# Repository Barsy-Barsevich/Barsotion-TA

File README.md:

# Barsotion-TA
Board computer for model rockets, the 11th board after Berkut

## ⚡️Features
- Dual-core 240MHz Xtensa processor (in ESP32-S3)
- 512 MB log flash
- Up to 8kHz IMU cycle frequency
- Barometer, thermometer, hygrometer
- Onboard DC-DC pull-up converter for servos
- 2.4GHz Wi-Fi / Bluetooth / BLE antenna

## ⚡️Manual
- [EA&TA_user_manual_revD.pdf (newest revision)](./Manual/EA&TA_user_manual_revD.pdf)
- [EA&TA_user_manual_revC.pdf](./Manual/EA&TA_user_manual_revC.pdf)
- [EA&TA_user_manual_preliminary_edition_revB.pdf](./Manual/EA&TA_user_manual_preliminary_edition_revB.pdf)
- [EA&TA_user_manual_preliminary_edition_revA.pdf](./Manual/EA&TA_user_manual_preliminary_edition_revA.pdf)

## ⚡️Software
- [EA & TA software packet](https://github.com/Barsy-Barsevich/Barsotion-xA-software)

## ⚡️Continious progress
- [Previous board: Barsotion-EA](https://github.com/Barsy-Barsevich/Barsotion-EA)
- [Previous board: Barsotion-AH4](https://github.com/Barsy-Barsevich/Barsotion-AH4)

## ⚡️Schematic
[Full electrical schematic in .pdf](./Schematic/Barsotion-TA_Schematic_v1.6.pdf)

## ⚡️Parameters
- Microcontroller: ESP32-S3FN8 (2x Xtensa LX7 core)
- Clock frequency: 240MHz
- Gyroscope: on-board ICM-42688-P (SPI, interrupt channel)
- Barometer: on-board, BMP388 (I2C)
- Hygrometer: on-board, AHT20 (I2C)
- Memory: 4Gbit SPI NAND Flash W25N04KVZEIG (Quad SPI)
- Quartz Gyroscope's ODR frequency stabilization
- 2.4GHz Wi-Fi / Bluetooth / BLE antenna

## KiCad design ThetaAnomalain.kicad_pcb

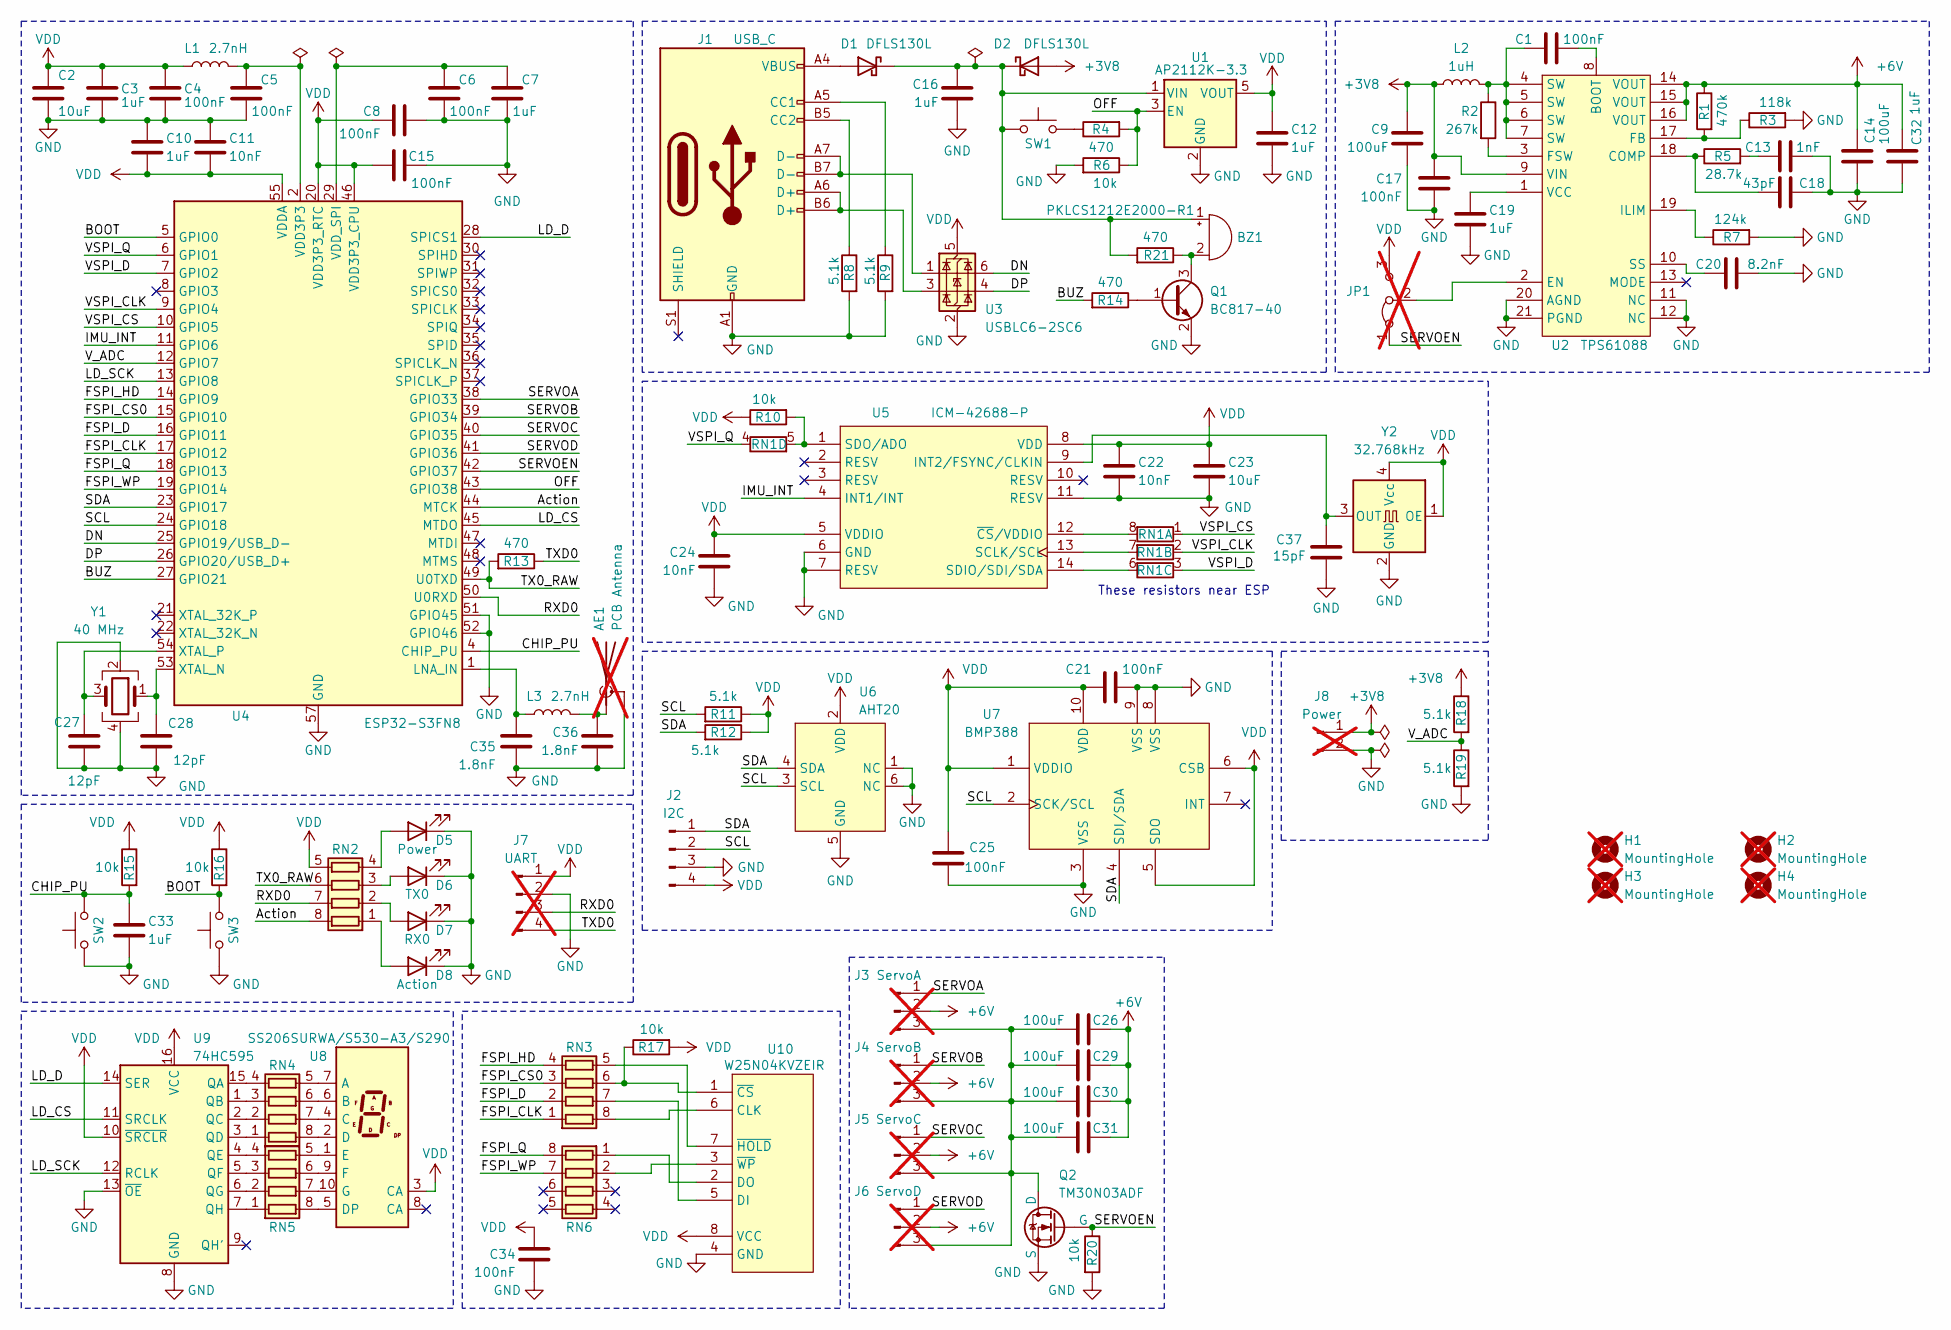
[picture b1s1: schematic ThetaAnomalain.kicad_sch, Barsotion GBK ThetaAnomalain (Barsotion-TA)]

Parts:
AE1: PCB Antenna; Texas_SWRA117D_2.4GHz_Right; not fitted
BZ1: PKLCS1212E2000-R1; Buzzer_Murata_PKLCS1212E; Mfr.Part PKLCS1212E2000-R1
C1, C4, C5, C6, C8, C15, C17, C21, C25, C34: 100nF; C_0402_1005Metric
C2, C23: 10uF; C_0402_1005Metric
C3, C7, C10, C12, C16, C19, C32, C33: 1uF; C_0402_1005Metric
C9, C14, C26, C29, C30, C31: 100uF; C_1206_3216Metric
C11, C22, C24: 10nF; C_0402_1005Metric
C13: 1nF; C_0402_1005Metric
C18: 43pF; C_0402_1005Metric
C20: 8.2nF; C_0402_1005Metric
C27, C28: 12pF; C_0402_1005Metric
C35, C36: 1.8nF; C_0402_1005Metric
C37: 15pF; C_0402_1005Metric
D1, D2: DFLS130L; D_PowerDI-123
D5: Power; LED_0603_1608Metric; Mfr.Part TJ-S1608CY6T5ALC9Y-A5
D6: TX0; LED_0603_1608Metric; Mfr.Part TJ-S1608CY6T5ALC9Y-A5
D7: RX0; LED_0603_1608Metric; Mfr.Part TJ-S1608CY6T5ALC9Y-A5
D8: Action; LED_0603_1608Metric; Mfr.Part TJ-S1608CY6T5ALC9Y-A5
H1, H2, H3, H4: MountingHole; MountingHole_3.2mm_M3_Pad_Via; not fitted
J1: USB_C; USB_C_Receptacle_GCT_USB4105-xx-A_16P_TopMnt_Horizontal; Mfr.Part TYPE C-DB-116PWB
J2: I2C; JST_GH_SM04B-GHS-TB_1x04-1MP_P1.25mm_Horizontal; Mfr.Part A1257WR-S-4P
J3: ServoA; JST_XH_B3B-XH-A_1x03_P2.50mm_Vertical; not fitted
J4: ServoB; JST_XH_B3B-XH-A_1x03_P2.50mm_Vertical; not fitted
J5: ServoC; JST_XH_B3B-XH-A_1x03_P2.50mm_Vertical; not fitted
J6: ServoD; JST_XH_B3B-XH-A_1x03_P2.50mm_Vertical; not fitted
J7: UART; JST_XH_B4B-XH-A_1x04_P2.50mm_Vertical; not fitted
J8: Power; Battery_3V7_Cable_connector_v2; not fitted
JP1: Jumper_3_Bridged12; SolderJumper-3_P1.3mm_Bridged12_Pad1.0x1.5mm_NumberLabels; not fitted
L1, L3: 2.7nH; L_0402_1005Metric
L2: 1uH; L_APV_APH0630; Mfr.Part APH0630T1R0M
Q1: BC817-40; SOT-23
Q2: TM30N03ADF; PDFN3x3-8L; Mfr.Part TM30N03ADF
R1: 470k; R_0402_1005Metric
R2: 267k; R_0402_1005Metric
R3: 118k; R_0402_1005Metric
R4, R13, R14, R21: 470; R_0402_1005Metric
R5: 28.7k; R_0402_1005Metric
R6, R10, R15, R16, R17, R20: 10k; R_0402_1005Metric
R7: 124k; R_0402_1005Metric
R8, R9, R11, R12, R18, R19: 5.1k; R_0402_1005Metric
RN1: 47; R_Array_Convex_4x0402
RN2, RN4, RN5: 1k; R_Array_Convex_4x0402
RN3, RN6: 0; R_Array_Convex_4x0402
SW1, SW2, SW3: TS-1187A-B-A-B; SW_Push_1P1T_XKB_TS-1187A; Mfr.Part TS-1187A-B-A-B
U1: AP2112K-3.3; SOT-23-5; Mfr.Part AP2112K-3.3TRG1
U2: TPS61088; RHL0020A; Mfr.Part TPS61088RHLR
U3: USBLC6-2SC6; SOT-23-6; Mfr.Part USBLC6-2SC6
U4: ESP32-S3FN8; QFN-56-1EP_7x7mm_P0.4mm_EP4x4mm; Mfr.Part ESP32-S3FN8
U5: ICM-42688-P; LGA-14_3x2.5mm_P0.5mm_LayoutBorder3x4y; Mfr.Part ICM-42688-P
U6: AHT20; Mfr.Part AHT20
U7: BMP388; BMP388_v2; Mfr.Part BMP388
U8: SS206SURWA/S530-A3/S290; SS206SURWA; Mfr.Part SS206SURWA/S530-A3/S290
U9: 74HC595; TSSOP-16_4.4x5mm_P0.65mm; Mfr.Part SN74HC595PWR
U10: W25N04KVZEIR; WSON-8-1EP_8x6mm_P1.27mm_EP3.4x4.3mm; Mfr.Part W25N04KVZEIR
Y1: 40 MHz; Crystal_SMD_3225-4Pin_3.2x2.5mm; Mfr.Part X322540MPB4SI
Y2: 32.768kHz; Oscillator_SMD_SeikoEpson_SG8002CE-4Pin_3.2x2.5mm; Mfr.Part OK2EL89CJI-111YLC-32.768K

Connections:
+3V8: C9.1, C17.1, D2.2 (A), J8.1, L2.1, R18.1, U2.9 (VIN)
+6V: C14.1, C26.1, C29.1, C30.1, C31.1, C32.1, J3.2, J4.2, J5.2, J6.2, R1.1, U2.14 (VOUT), U2.15 (VOUT), U2.16 (VOUT)
/Action: RN2.8 (R1.2), U4.44 (MTCK)
/BOOT: R16.2, SW3.2, U4.5 (GPIO0)
/BUZ: R14.2, U4.27 (GPIO21)
/CHIP_PU: C33.1, R15.2, SW2.2, U4.4 (CHIP_PU)
/DN: U3.6 (I/O1), U4.25 (GPIO19/USB_D-)
/DP: U3.4 (I/O2), U4.26 (GPIO20/USB_D+)
/FSPI_CLK: RN3.1 (R1.1), U4.17 (GPIO12)
/FSPI_CS0: RN3.3 (R3.1), U4.15 (GPIO10)
/FSPI_D: RN3.2 (R2.1), U4.16 (GPIO11)
/FSPI_HD: RN3.4 (R4.1), U4.14 (GPIO9)
/FSPI_Q: RN6.8 (R1.2), U4.18 (GPIO13)
/FSPI_WP: RN6.7 (R2.2), U4.19 (GPIO14)
/IMU_INT: U4.11 (GPIO6), U5.4 (INT1/INT)
/LD_CS: U4.45 (MTDO), U9.11 (SRCLK)
/LD_D: U4.28 (SPICS1), U9.14 (SER)
/LD_SCK: U4.13 (GPIO8), U9.12 (RCLK)
/OFF: R4.2, R6.1, U1.3 (EN), U4.43 (GPIO38)
/RXD0: J7.3, RN2.7 (R2.2), U4.50 (U0RXD)
/SCL: J2.2, R11.2, U4.24 (GPIO18), U6.3 (SCL), U7.2 (SCK/SCL)
/SDA: J2.1, R12.2, U4.23 (GPIO17), U6.4 (SDA), U7.4 (SDI/SDA)
/SERVOA: J3.1, U4.38 (GPIO33)
/SERVOB: J4.1, U4.39 (GPIO34)
/SERVOC: J5.1, U4.40 (GPIO35)
/SERVOD: J6.1, U4.41 (GPIO36)
/SERVOEN: JP1.1 (A), Q2.2 (G), R20.1, U4.42 (GPIO37)
/TX0_RAW: R13.2, RN2.6 (R3.2), U4.49 (U0TXD)
/TXD0: J7.4, R13.1
/VSPI_CLK: RN1.2 (R2.1), U4.9 (GPIO4)
/VSPI_CS: RN1.1 (R1.1), U4.10 (GPIO5)
/VSPI_D: RN1.3 (R3.1), U4.7 (GPIO2)
/VSPI_Q: RN1.4 (R4.1), U4.6 (GPIO1)
/V_ADC: R18.2, R19.1, U4.12 (GPIO7)
GND: AE1.2 (Shield), C2.2, C3.2, C4.2, C5.2, C6.2, C7.2, C8.2, C9.2, C10.1, C11.1, C12.2, C13.1, C14.2, C15.2, C16.2, C17.2, C18.1, C19.2, C20.1, C21.2, C22.2, C23.2, C24.2, C25.1, C27.2, C28.2, C32.2, C33.2, C34.2, C35.2, C36.2, C37.2, D5.1 (K), D6.1 (K), D7.1 (K), D8.1 (K), J1.A1 (GND), J1.A12 (GND), J1.B1 (GND), J1.B12 (GND), J2.3, J7.2, J8.2, Q1.2 (E), Q2.3 (S), R3.2, R6.2, R7.2, R8.2, R9.2, R19.2, R20.2, SW2.1, SW3.1, U1.2 (GND), U2.11 (NC), U2.12 (NC), U2.20 (AGND), U2.21 (PGND), U3.2 (GND), U4.51 (GPIO45), U4.52 (GPIO46), U4.57 (GND), U5.6 (GND), U5.7 (RESV), U5.11 (RESV), U6.1 (NC), U6.5 (GND), U6.6 (NC), U7.3 (VSS), U7.8 (VSS), U7.9 (VSS), U9.8 (GND), U9.13 (~OE), U10.4 (GND), Y1.2, Y1.4, Y2.2 (GND)
unnamed: AE1.1 (A), C36.1, L3.2
unnamed: BZ1.1 (+), C16.1, D1.1 (K), D2.1 (K), R21.2, SW1.1, U1.1 (VIN)
unnamed: BZ1.2 (-), Q1.3 (C), R21.1
unnamed: C1.2, L2.2, R2.1, U2.4 (SW), U2.5 (SW), U2.6 (SW), U2.7 (SW)
unnamed: C5.1, L1.2, U4.2 (VDD3P3), U4.3 (VDD3P3)
unnamed: C13.2, R5.2
unnamed: D1.2 (A), J1.A4 (VBUS), J1.A9 (VBUS), J1.B4 (VBUS), J1.B9 (VBUS)
unnamed: D5.2 (A), RN2.4 (R4.1)
unnamed: D6.2 (A), RN2.3 (R3.1)
unnamed: D7.2 (A), RN2.2 (R2.1)
unnamed: D8.2 (A), RN2.1 (R1.1)
unnamed: J1.A5 (CC1), R9.1
unnamed: J1.B5 (CC2), R8.1
unnamed: J1.A6 (D+), J1.B6 (D+), U3.3 (I/O2)
unnamed: J1.A7 (D-), J1.B7 (D-), U3.1 (I/O1)
unnamed: C26.2, C29.2, C30.2, C31.2, J3.3, J4.3, J5.3, J6.3, Q2.1 (D)
unnamed: JP1.2 (C), U2.2 (EN)
unnamed: Q1.1 (B), R14.1
unnamed: R4.1, SW1.2
unnamed: RN1.8 (R1.2), U5.12 (~CS/VDDIO)
unnamed: RN1.7 (R2.2), U5.13 (SCLK/SCL)
unnamed: RN1.6 (R3.2), U5.14 (SDIO/SDI/SDA)
unnamed: R10.2, RN1.5 (R4.2), U5.1 (SDO/ADO)
unnamed: RN3.8 (R1.2), U10.6 (CLK)
unnamed: RN3.7 (R2.2), U10.5 (DI)
unnamed: R17.1, RN3.6 (R3.2), U10.1 (~CS)
unnamed: RN3.5 (R4.2), U10.7 (~HOLD)
unnamed: RN4.1 (R1.1), U9.3 (QD)
unnamed: RN4.8 (R1.2), U8.2 (D)
unnamed: RN4.2 (R2.1), U9.2 (QC)
unnamed: RN4.7 (R2.2), U8.4 (C)
unnamed: RN4.3 (R3.1), U9.1 (QB)
unnamed: RN4.6 (R3.2), U8.6 (B)
unnamed: RN4.4 (R4.1), U9.15 (QA)
unnamed: RN4.5 (R4.2), U8.7 (A)
unnamed: RN5.1 (R1.1), U9.7 (QH)
unnamed: RN5.8 (R1.2), U8.5 (DP)
unnamed: RN5.2 (R2.1), U9.6 (QG)
unnamed: RN5.7 (R2.2), U8.10 (G)
unnamed: RN5.3 (R3.1), U9.5 (QF)
unnamed: RN5.6 (R3.2), U8.9 (F)
unnamed: RN5.4 (R4.1), U9.4 (QE)
unnamed: RN5.5 (R4.2), U8.1 (E)
unnamed: RN6.1 (R1.1), U10.2 (DO)
unnamed: RN6.2 (R2.1), U10.3 (~WP)
unnamed: C1.1, U2.8 (BOOT)
unnamed: C18.2, R5.1, U2.18 (COMP)
unnamed: R1.2, R3.1, U2.17 (FB)
unnamed: R2.2, U2.3 (FSW)
unnamed: R7.1, U2.19 (ILIM)
unnamed: C20.2, U2.10 (SS)
unnamed: C19.1, U2.1 (VCC)
unnamed: C35.1, L3.1, U4.1 (LNA_IN)
unnamed: C6.1, C7.1, U4.29 (VDD_SPI)
unnamed: C28.1, U4.53 (XTAL_N), Y1.1
unnamed: C27.1, U4.54 (XTAL_P), Y1.3
unnamed: C37.1, U5.9 (INT2/FSYNC/CLKIN), Y2.3 (OUT)
VDD: C2.1, C3.1, C4.1, C8.1, C10.2, C11.2, C12.1, C15.1, C21.1, C22.1, C23.1, C24.1, C25.2, C34.1, J2.4, J7.1, JP1.3 (B), L1.1, R10.1, R11.1, R12.1, R15.1, R16.1, R17.2, RN2.5 (R4.2), U1.5 (VOUT), U3.5 (VBUS), U4.20 (VDD3P3_RTC), U4.46 (VDD3P3_CPU), U4.55 (VDDA), U4.56 (VDDA), U5.5 (VDDIO), U5.8 (VDD), U6.2 (VDD), U7.1 (VDDIO), U7.5 (SDO), U7.6 (CSB), U7.10 (VDD), U8.3 (CA), U9.10 (~SRCLR), U9.16 (VCC), U10.8 (VCC), Y2.1 (OE), Y2.4 (Vcc)

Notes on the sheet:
These resistors near ESP

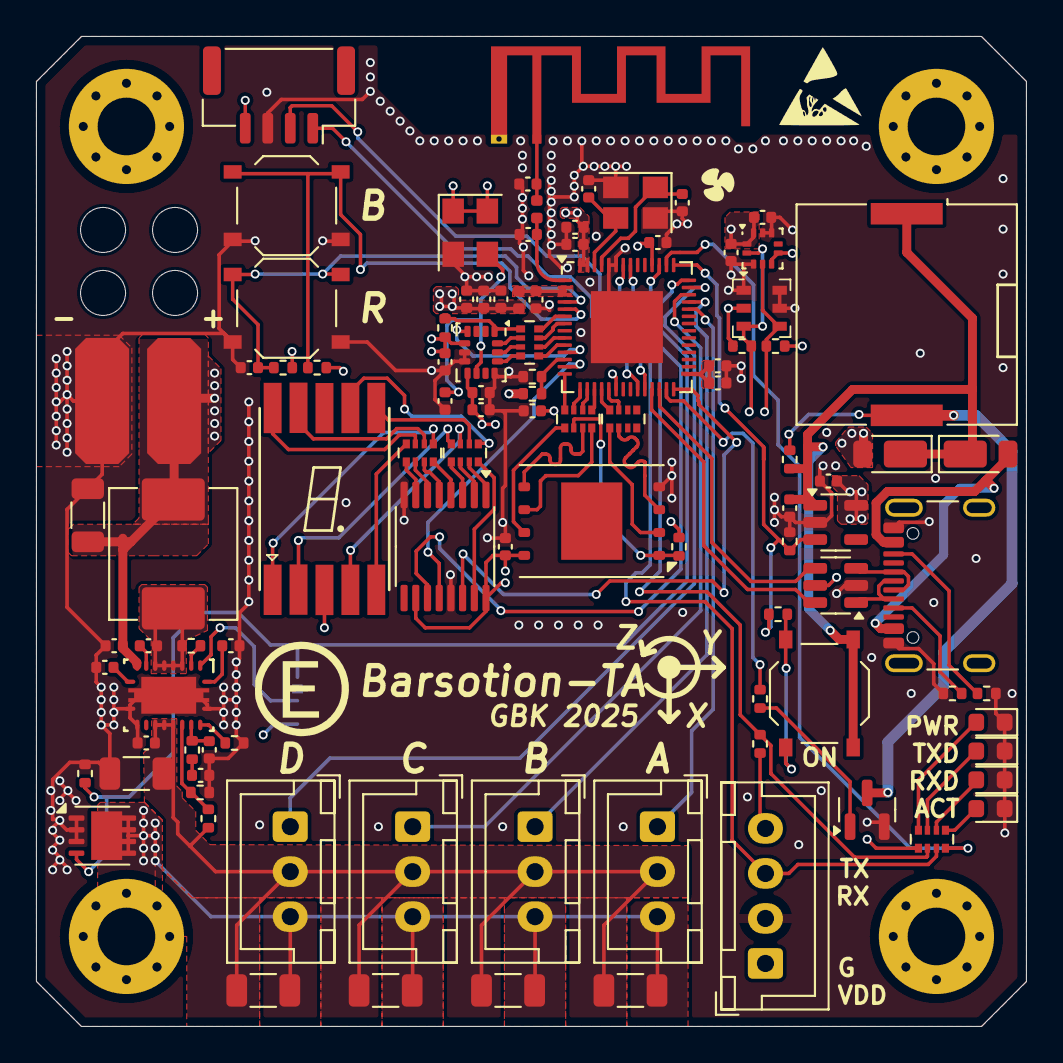
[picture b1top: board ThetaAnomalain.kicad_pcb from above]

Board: 4 copper layers, 55.0 x 55.0 mm, 105 parts (1 on the bottom side), 93 nets.

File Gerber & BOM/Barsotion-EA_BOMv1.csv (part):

"Reference","Value","Datasheet","Footprint","Qty","DNP","Описание","Mfr.Part"
"BZ1","CMT-8504-100","https://www.lcsc.com/datasheet/lcsc_datasheet_2410010302_Mur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","Buzzer_Beeper:MagneticBuzzer_CUI_CMT-8504-100-SMT","1","","Buzzer, polarized","CMT-8504-100"
"C1","100nF","~","Capacitor_SMD:C_0402_1005Metric","1","","Unpolarized capacitor",""
"C2","10uF","~","Capacitor_SMD:C_0402_1005Metric","1","","Unpolarized capacitor",""
"C3","1uF","~","Capacitor_SMD:C_0402_1005Metric","1","","Unpolarized capacitor",""
"C4","100nF","~","Capacitor_SMD:C_0402_1005Metric","1","","Unpolarized capacitor",""
"C5","100nF","~","Capacitor_SMD:C_0402_1005Metric","1","","Unpolarized capacitor",""
"C6","100nF","~","Capacitor_SMD:C_0402_1005Metric","1","","Unpolarized capacitor",""
"C7","1uF","~","Capacitor_SMD:C_0402_1005Metric","1","","Unpolarized capacitor",""
"C8","100nF","~","Capacitor_SMD:C_0402_1005Metric","1","","Unpolarized capacitor",""
"C9","100uF","~","Capacitor_SMD:C_1206_3216Metric","1","","Unpolarized capacitor",""
"C10","1uF","~","Capacitor_SMD:C_0402_1005Metric","1","","Unpolarized capacitor",""
"C11","10nF","~","Capacitor_SMD:C_0402_1005Metric","1","","Unpolarized capacitor",""
"C12","1uF","~","Capacitor_SMD:C_0402_1005Metric","1","","Unpolarized capacitor",""
"C13","1nF","~","Capacitor_SMD:C_0402_1005Metric","1","","Unpolarized capacitor",""
"C14","100uF","~","Capacitor_SMD:C_1206_3216Metric","1","","Unpolarized capacitor",""
"C15","100nF","~","Capacitor_SMD:C_0402_1005Metric","1","","Unpolarized capacitor",""
"C16","1uF","~","Capacitor_SMD:C_0402_1005Metric","1","","Unpolarized capacitor",""
"C17","100nF","~","Capacitor_SMD:C_0402_1005Metric","1","","Unpolarized capacitor",""
"C18","43pF","~","Capacitor_SMD:C_0402_1005Metric","1","","Unpolarized capacitor",""
"C19","1uF","~","Capacitor_SMD:C_0402_1005Metric","1","","Unpolarized capacitor",""
"C20","8.2nF","~","Capacitor_SMD:C_0402_1005Metric","1","","Unpolarized capacitor",""
"C21","100nF","~","Capacitor_SMD:C_0402_1005Metric","1","","Unpolarized capacitor",""
"C22","10nF","~","Capacitor_SMD:C_0402_1005Metric","1","","Unpolarized capacitor",""
"C23","10uF","~","Capacitor_SMD:C_0402_1005Metric","1","","Unpolarized capacitor",""
"C24","10nF","~","Capacitor_SMD:C_0402_1005Metric","1","","Unpolarized capacitor",""
"C25","100nF","~","Capacitor_SMD:C_0402_1005Metric","1","","Unpolarized capacitor",""
"C26","100uF","~","Capacitor_SMD:C_1206_3216Metric","1","","Unpolarized capacitor",""
"C27","12pF","~","Capacitor_SMD:C_0402_1005Metric","1","","Unpolarized capacitor",""
"C28","12pF","~","Capacitor_SMD:C_0402_1005Metric","1","","Unpolarized capacitor",""
"C29","100uF","~","Capacitor_SMD:C_1206_3216Metric","1","","Unpolarized capacitor",""
"C30","100uF","~","Capacitor_SMD:C_1206_3216Metric","1","","Unpolarized capacitor",""
"C31","100uF","~","Capacitor_SMD:C_1206_3216Metric","1","","Unpolarized capacitor",""
"C32","1uF","~","Capacitor_SMD:C_0402_1005Metric","1","","Unpolarized capacitor",""
"C33","1uF","~","Capacitor_SMD:C_0402_1005Metric","1","","Unpolarized capacitor",""
"C34","100nF","~","Capacitor_SMD:C_0402_1005Metric","1","","Unpolarized capacitor",""
"C35","1.8nF","~","Capacitor_SMD:C_0402_1005Metric","1","","Unpolarized capacitor",""
"C36","1.8nF","~","Capacitor_SMD:C_0402_1005Metric","1","","Unpolarized capacitor",""
"C37","15pF","~","Capacitor_SMD:C_0402_1005Metric","1","","Unpolarized capacitor",""
"D1","DFLS130L","~","Diode_SMD:D_PowerDI-123","1","","Schottky diode",""
"D2","DFLS130L","~","Diode_SMD:D_PowerDI-123","1","","Schottky diode",""
"D3","1N4148W","https://www.vishay.com/docs/85748/1n4148w.pdf","Diode_SMD:D_SOD-123","1","","75V 0.15A Fast Switching Diode, SOD-123","1N4148W"
"D5","Power","~","LED_SMD:LED_0603_1608Metric","1","","Yellow Light emitting diode","TJ-S1608CY6T5ALC9Y-A5"
"D6","TX0","~","LED_SMD:LED_0603_1608Metric","1","","Yellow Light emitting diode","TJ-S1608CY6T5ALC9Y-A5"
"D7","RX0","~","LED_SMD:LED_0603_1608Metric","1","","Yellow Light emitting diode","TJ-S1608CY6T5ALC9Y-A5"
"D8","Action","~","LED_SMD:LED_0603_1608Metric","1","","Yellow Light emitting diode","TJ-S1608CY6T5ALC9Y-A5"
"J1","USB_C","https://www.usb.org/sites/default/files/documents/usb_type-c.zip","Connector_USB:USB_C_Receptacle_GCT_USB4105-xx-A_16P_TopMnt_Horizontal","1","","USB 2.0-only 16P Type-C Receptacle connector, mfr part TYPE C-DB-116PWB","TYPE C-DB-116PWB"
"J2","I2C","~","Connector_JST:JST_GH_SM04B-GHS-TB_1x04-1MP_P1.25mm_Horizontal","1","","Generic connector, single row, 01x04, script generated","A1257WR-S-4P"
"L1","2.7nH","https://www.lcsc.com/datasheet/lcsc_datasheet_2409302232_APV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","Inductor_SMD:L_0402_1005Metric","1","","Inductor",""
"L2","1uH","https://www.lcsc.com/datasheet/lcsc_datasheet_2409302232_APV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","Inductor_SMD:L_APV_APH0630","1","","Power inductor","APH0630T1R0M"
"L3","2.7nH","https://www.lcsc.com/datasheet/lcsc_datasheet_2409302232_APV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","Inductor_SMD:L_0402_1005Metric","1","","Inductor",""
"Q1","BC817-40","https://www.onsemi.com/pub/Collateral/BC818-D.pdf","Package_TO_SOT_SMD:SOT-23","1","","0.8A Ic, 45V Vce, NPN Transistor, SOT-23",""
"Q2","NMOS","https://ngspice.sourceforge.io/docs/ngspice-html-manual/manu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","CustomPackage:PDFN3x3-8L","1","","N-MOSFET transistor, drain/source/gate",""
"R1","470k","~","Resistor_SMD:R_0402_1005Metric","1","","Resistor",""
"R2","267k","~","Resistor_SMD:R_0402_1005Metric","1","","Resistor",""
"R3","118k","~","Resistor_SMD:R_0402_1005Metric","1","","Resistor",""
"R4","100","~","Resistor_SMD:R_0402_1005Metric","1","","Resistor",""
"R5","28.7k","~","Resistor_SMD:R_0402_1005Metric","1","","Resistor",""
"R6","10k","~","Resistor_SMD:R_0402_1005Metric","1","","Resistor",""
"R7","124k","~","Resistor_SMD:R_0402_1005Metric","1","","Resistor",""
"R8","5.1k","~","Resistor_SMD:R_0402_1005Metric","1","","Resistor",""
"R9","5.1k","~","Resistor_SMD:R_0402_1005Metric","1","","Resistor",""
"R10","10k","~","Resistor_SMD:R_0402_1005Metric","1","","Resistor",""
"R11","5.1k","~","Resistor_SMD:R_0402_1005Metric","1","","Resistor",""
"R12","5.1k","~","Resistor_SMD:R_0402_1005Metric","1","","Resistor",""
"R13","470","~","Resistor_SMD:R_0402_1005Metric","1","","Resistor",""
"R14","470","~","Resistor_SMD:R_0402_1005Metric","1","","Resistor",""
"R15","10k","~","Resistor_SMD:R_0402_1005Metric","1","","Resistor",""
"R16","10k","~","Resistor_SMD:R_0402_1005Metric","1","","Resistor",""
"R17","10k","~","Resistor_SMD:R_0402_1005Metric","1","","Resistor",""
"R18","5.1k","~","Resistor_SMD:R_0402_1005Metric","1","","Resistor",""
"R19","5.1k","~","Resistor_SMD:R_0402_1005Metric","1","","Resistor",""
"R20","10k","~","Resistor_SMD:R_0402_1005Metric","1","","Resistor",""
"RN1","47","~","Resistor_SMD:R_Array_Convex_4x0402","1","","4 resistor network, parallel topology, split",""
"RN2","1k","~","Resistor_SMD:R_Array_Convex_4x0402","1","","4 resistor network, parallel topology",""
"RN3","0","~","Resistor_SMD:R_Array_Convex_4x0402","1","","4 resistor network, parallel topology",""
"RN4","1k","~","Resistor_SMD:R_Array_Convex_4x0402","1","","4 resistor network, parallel topology",""
"RN5","1k","~","Resistor_SMD:R_Array_Convex_4x0402","1","","4 resistor network, parallel topology",""
"RN6","0","~","Resistor_SMD:R_Array_Convex_4x0402","1","","4 resistor network, parallel topology",""
"SW1","TS-1187A-B-A-B","~","Button_Switch_SMD:SW_Push_1P1T_XKB_TS-1187A","1","","TS-1187A-B-A-B","TS-1187A-B-A-B"
"SW2","TS-1187A-B-A-B","~","Button_Switch_SMD:SW_Push_1P1T_XKB_TS-1187A","1","","TS-1187A-B-A-B","TS-1187A-B-A-B"
"SW3","TS-1187A-B-A-B","~","Button_Switch_SMD:SW_Push_1P1T_XKB_TS-1187A","1","","TS-1187A-B-A-B","TS-1187A-B-A-B"
"U1","AP2112K-3.3","https://www.diodes.com/assets/Datasheets/AP2112.pdf","Package_TO_SOT_SMD:SOT-23-5","1","","600mA low dropout linear regulator, with enable pin, 3.8V-6V input voltage range, 3.3V fixed positive output, SOT-23-5","AP2112K-3.3TRG1"
"U2","TPS61088","","UltraLibrarian:RHL0020A","1","","Texas Instruments DC-DC Pullup converter","TPS61088RHLR "
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
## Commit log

2025-03-31 Create LICENSE
2025-04-02 implementing EA project
2025-04-08 v1.3
2025-04-13 v1.5
2025-04-23 topology photoes added
2025-04-23 topology update
2025-04-23 update topology
2025-04-25 dimentions added
2025-04-25 adding blocksheme
2025-04-25 new photo explained
2025-05-06 v1.6
2025-05-11 manual added + readme update
2025-05-11 other sw rep name
2025-05-11 readme photo fix
2025-05-29 new software packet link
2025-05-29 manual addition
2025-06-03 default software added
2025-06-15 Manual rev.B addition
2025-06-15 readme update
2025-07-18 revD manual
2025-12-09 box photos added
